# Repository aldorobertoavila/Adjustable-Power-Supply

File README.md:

# Adjustable-Power-Supply
A linear power supply with input voltage (Vin) from 3-40V, output voltage (Vout) from 1.25-37V & fixed-current of 1A, based on a LM317 voltage regulator.

## Credits
Thanks to the GrabCAD community for creating the following models:

* [Pierre Gleizes](https://grabcad.com/library/10k-rotary-potentiometer-1) - 10K Potentiometer
* [Sig Elso](https://grabcad.com/library/degson-dg306-series-5-0-terminal-block-pack-1) - Terminal Block

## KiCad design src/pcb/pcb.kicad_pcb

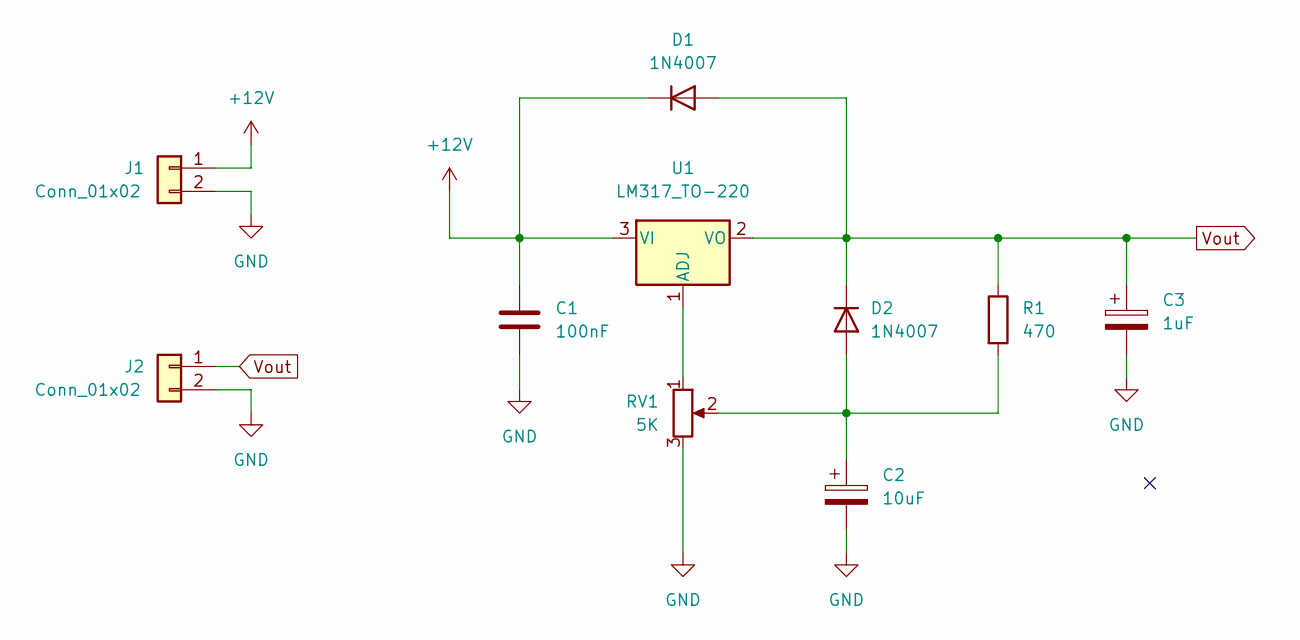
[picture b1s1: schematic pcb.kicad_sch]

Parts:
C1: 100nF; C_Disc_D5.0mm_W2.5mm_P5.00mm
C2: 10uF; C_Radial_D4.0mm_H7.0mm_P1.50mm
C3: 1uF; C_Radial_D4.0mm_H7.0mm_P1.50mm
D1, D2: 1N4007; D_DO-41_SOD81_P10.16mm_Horizontal
J1, J2: Conn_01x02; TerminalBlock_bornier-2_P5.08mm
R1: 470; R_Axial_DIN0207_L6.3mm_D2.5mm_P10.16mm_Horizontal
RV1: 5K; Potentiometer_Alps_RK163_Single_Horizontal
U1: LM317_TO-220; TO-220-3_Vertical

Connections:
+12V: C1.1, D1.1 (K), J1.1, U1.3 (VI)
GND: C1.2, C2.2, C3.2, J1.2, J2.2, RV1.3
unnamed: C2.1, D2.2 (A), R1.2, RV1.2
unnamed: RV1.1, U1.1 (ADJ)
Vout: C3.1, D1.2 (A), D2.1 (K), J2.1, R1.1, U1.2 (VO)

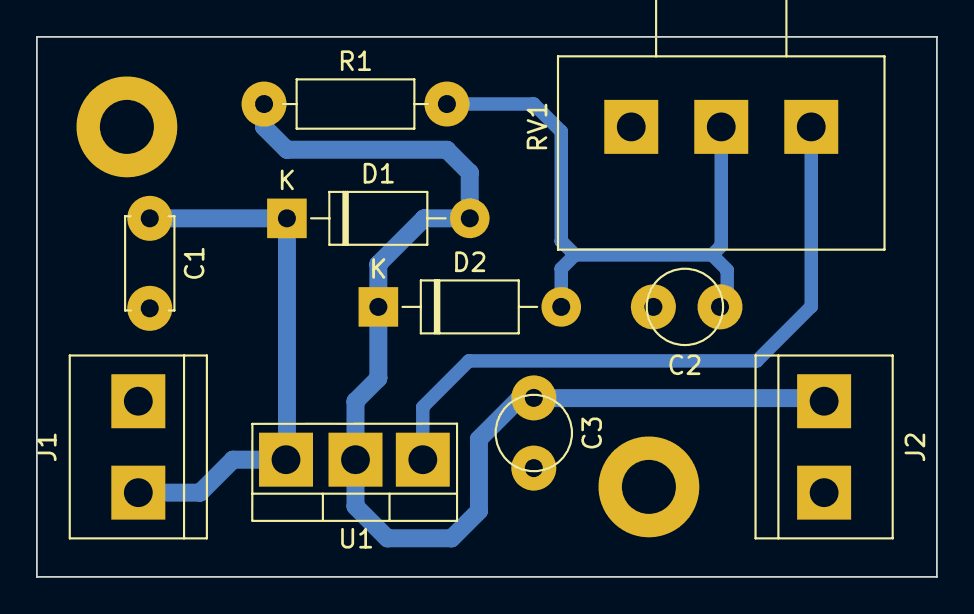
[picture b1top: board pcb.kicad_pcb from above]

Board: 2 copper layers, 50.0 x 30.0 mm, 10 parts (0 on the bottom side), 5 nets.

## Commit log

2022-09-14 Setup KiCad project
2022-09-20 Add: Schematic Circuit
2022-09-22 Add: PCB layout
2022-09-23 Fix: Remove island
    Add: Terminal Block STEP
    Add: Potentiometer STEP
2022-10-30 Fix: Pad Size
2022-11-04 Fix: Hole Sizes
